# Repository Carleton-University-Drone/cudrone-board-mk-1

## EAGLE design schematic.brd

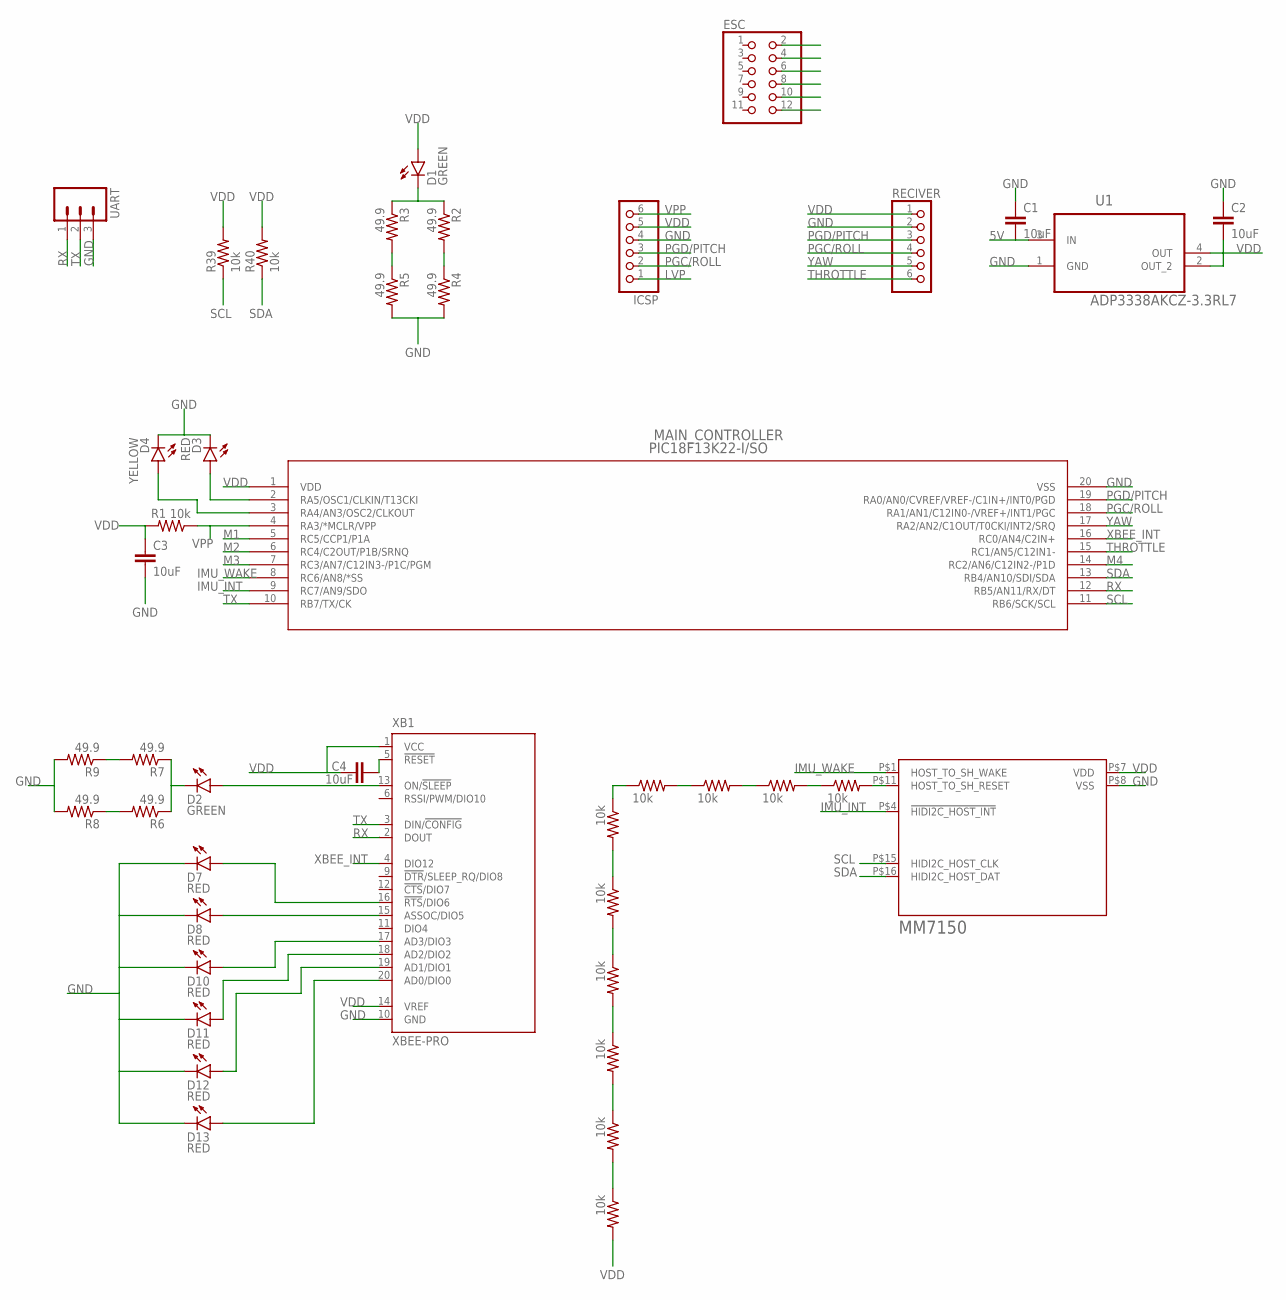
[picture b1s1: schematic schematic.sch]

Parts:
C1, C2, C3, C4: 10uF; 1210
D1, D2: GREEN; LED-1206
D3, D7, D8, D10, D11, D12, D13: RED; LED-1206
D4: YELLOW; LED-1206
ESC: PINHD-2X6; 2X06
ICSP: PINHD-1X6/90; 1X06/90
IMU: MM7150; LANDPATTERN
MAIN_CONTROLLER: PIC18F13K22-I/SO; PIC18F13K22-X/SO
R1, R10, R11, R12, R13, R14, R15, R16, R17, R18, R19, R39, R40: 10k; 0402-RES
R2, R3, R4, R5, R6, R7, R8, R9: 49.9; 0402-RES
RECIVER: PINHD-1X6; 1X06
U1: ADP3338AKCZ-3.3RL7; SOT230P700X180-4N
UART: M03LONGPADS; 1X03_LONGPADS
XB1: XBEE-PRO

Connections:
5V: C1.2, ESC.2, U1.3 (IN)
GND: C1.1, C2.1, C3.2, D3.C, D4.C, D7.C, D8.C, D10.C, D11.C, D12.C, D13.C, ESC.4, ICSP.4, IMU.P$8 (VSS), MAIN_CONTROLLER.20 (VSS), R4.2, R5.2, R8.2, R9.2, RECIVER.2, U1.1 (GND), UART.3, XB1.10 (GND)
IMU_INT: IMU.P$4 (!HIDI2C_HOST_INT), MAIN_CONTROLLER.9 (RC7/AN9/SDO)
IMU_WAKE: IMU.P$1 (HOST_TO_SH_WAKE), MAIN_CONTROLLER.8 (RC6/AN8/*SS)
LVP: ICSP.1
M1: ESC.6, MAIN_CONTROLLER.5 (RC5/CCP1/P1A)
M2: ESC.8, MAIN_CONTROLLER.6 (RC4/C2OUT/P1B/SRNQ)
M3: ESC.10, MAIN_CONTROLLER.7 (RC3/AN7/C12IN3-/P1C/PGM)
M4: ESC.12, MAIN_CONTROLLER.14 (RC2/AN6/C12IN2-/P1D)
unnamed: D7.A, XB1.16 (!RTS!/DIO6)
unnamed: R3.2, R5.1
unnamed: R2.2, R4.1
unnamed: D1.C, R2.1, R3.1
unnamed: C4.1, XB1.5 (!RESET)
unnamed: R7.2, R9.1
unnamed: R6.2, R8.1
unnamed: D2.C, R6.1, R7.1
unnamed: D2.A, XB1.13 (ON/!SLEEP)
unnamed: IMU.P$11 (HOST_TO_SH_RESET), R10.2
unnamed: R10.1, R11.2
unnamed: R11.1, R12.2
unnamed: R12.1, R13.2
unnamed: R13.1, R14.1
unnamed: R14.2, R15.1
unnamed: R15.2, R16.1
unnamed: R16.2, R17.1
unnamed: R17.2, R18.1
unnamed: R18.2, R19.1
unnamed: D10.A, XB1.17 (AD3/DIO3)
unnamed: D11.A, XB1.18 (AD2/DIO2)
unnamed: D12.A, XB1.19 (AD1/DIO1)
unnamed: D13.A, XB1.20 (AD0/DIO0)
unnamed: D3.A, MAIN_CONTROLLER.2 (RA5/OSC1/CLKIN/T13CKI)
unnamed: D4.A, MAIN_CONTROLLER.3 (RA4/AN3/OSC2/CLKOUT)
unnamed: D8.A, XB1.15 (ASSOC/DIO5)
PGC/ROLL: ICSP.2, MAIN_CONTROLLER.18 (RA1/AN1/C12IN0-/VREF+/INT1/PGC), RECIVER.4
PGD/PITCH: ICSP.3, MAIN_CONTROLLER.19 (RA0/AN0/CVREF/VREF-/C1IN+/INT0/PGD), RECIVER.3
RX: MAIN_CONTROLLER.12 (RB5/AN11/RX/DT), UART.1, XB1.2 (DOUT)
SCL: IMU.P$15 (HIDI2C_HOST_CLK), MAIN_CONTROLLER.11 (RB6/SCK/SCL), R39.1
SDA: IMU.P$16 (HIDI2C_HOST_DAT), MAIN_CONTROLLER.13 (RB4/AN10/SDI/SDA), R40.1
THROTTLE: MAIN_CONTROLLER.15 (RC1/AN5/C12IN1-), RECIVER.6
TX: MAIN_CONTROLLER.10 (RB7/TX/CK), UART.2, XB1.3 (DIN/!CONFIG)
VDD: C2.2, C3.1, C4.2, D1.A, ICSP.5, IMU.P$7 (VDD), MAIN_CONTROLLER.1 (VDD), R1.2, R19.2, R39.2, R40.2, RECIVER.1, U1.2 (OUT_2), U1.4 (OUT), XB1.1 (VCC), XB1.14 (VREF)
VPP: ICSP.6, MAIN_CONTROLLER.4 (RA3/*MCLR/VPP), R1.1
XBEE_INT: MAIN_CONTROLLER.16 (RC0/AN4/C2IN+), XB1.4 (DIO12)
YAW: MAIN_CONTROLLER.17 (RA2/AN2/C1OUT/T0CKI/INT2/SRQ), RECIVER.5

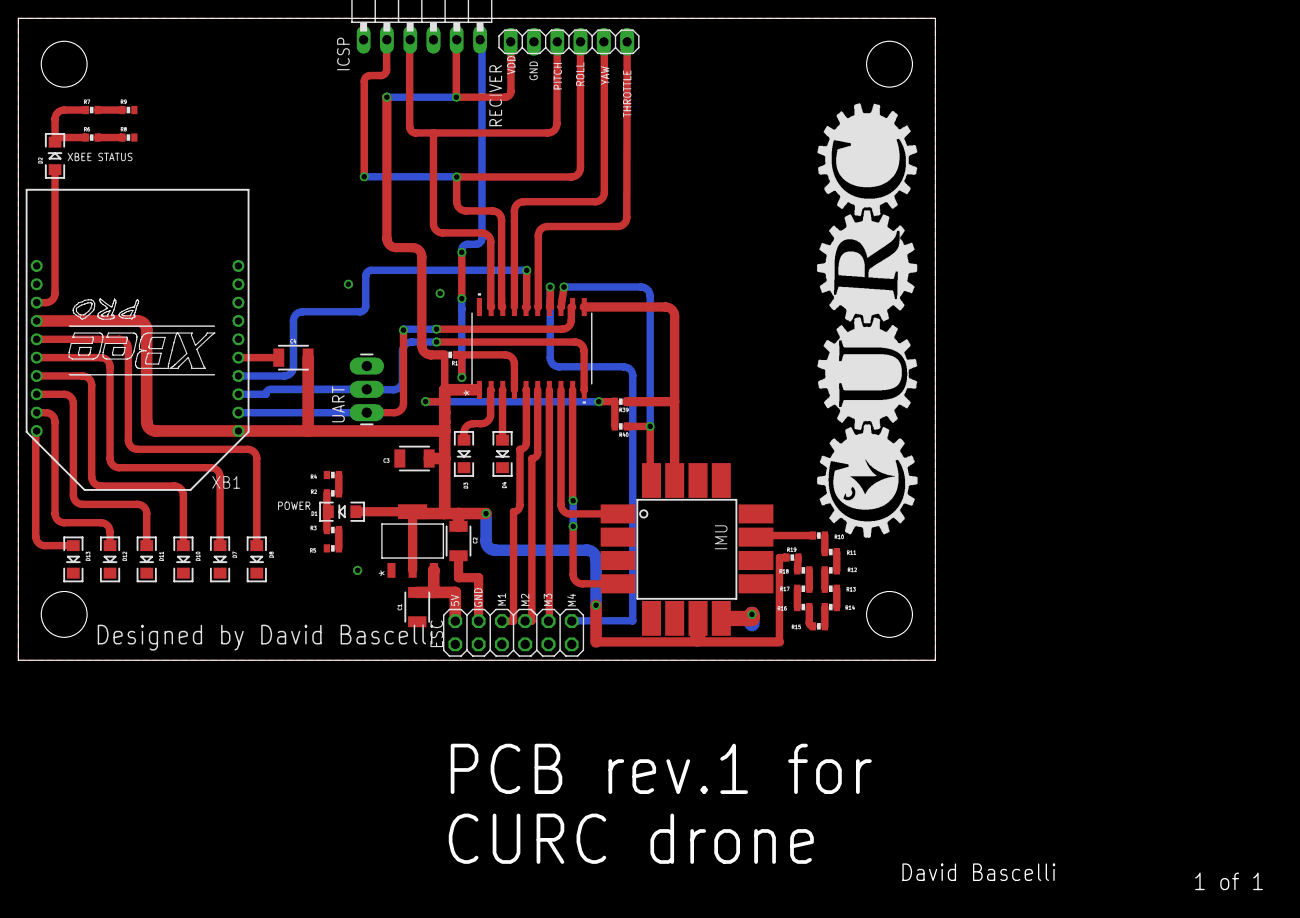
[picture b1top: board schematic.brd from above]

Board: 2 copper layers, 100.0 x 70.0 mm, 44 parts (0 on the bottom side), 45 nets.

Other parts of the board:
U$1: A5L-LOC

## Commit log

2016-06-13 :circus_tent: Added .gitattributes & .gitignore files
2016-06-13 Created repo, basic board dimensions and controller
2016-06-14 Created schematic for ccentral processor and PWM IO
2016-06-30 Attached IMU and XBEE in schematic. Schematic is now done unless the extra outputs from the xbee are needed
2016-07-02 Added missing connections for IMU and XBEE. Added inturrupt pin for XBEE.
2016-07-02 Inital placement of components
2016-07-02 Inital laying of all traces. Jumpers still need to be added
2016-07-03 Repositioned components to reduce number of jumber cables needed
2016-07-05 Added several missing components, rearanged some components to make routing easier and added last jumper cables. Board layout is theretically done now
2016-07-06 Rearanged several components to remove some jumper cables, added led's to unused pins on xbee and controller
2016-07-09 minor fix
2016-07-09 Removed jumper's from schematic and prepared for two layer board
2016-07-09 Made the two layer board.
2016-07-09 Added curc logo to silkscreen
2016-07-09 Mitered all wires.
2016-07-09 Straightened out some wires
2016-07-09 Added designer's name to pcb
2016-07-09 Cleaned up the silkscreen and added more labels
2016-07-20 Fixed a mixup in the pinout for the ICSP
2016-07-20 Reversed ICSP pins so programmer will be right way up
2016-10-12 Added Named to pins
    Kassem’s first commit

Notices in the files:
parts and their libraries:
SparkFun-LED: Licensing: Creative Commons ShareAlike 4.0 International - https://creativecommons.org/licenses/by-sa/4.0
